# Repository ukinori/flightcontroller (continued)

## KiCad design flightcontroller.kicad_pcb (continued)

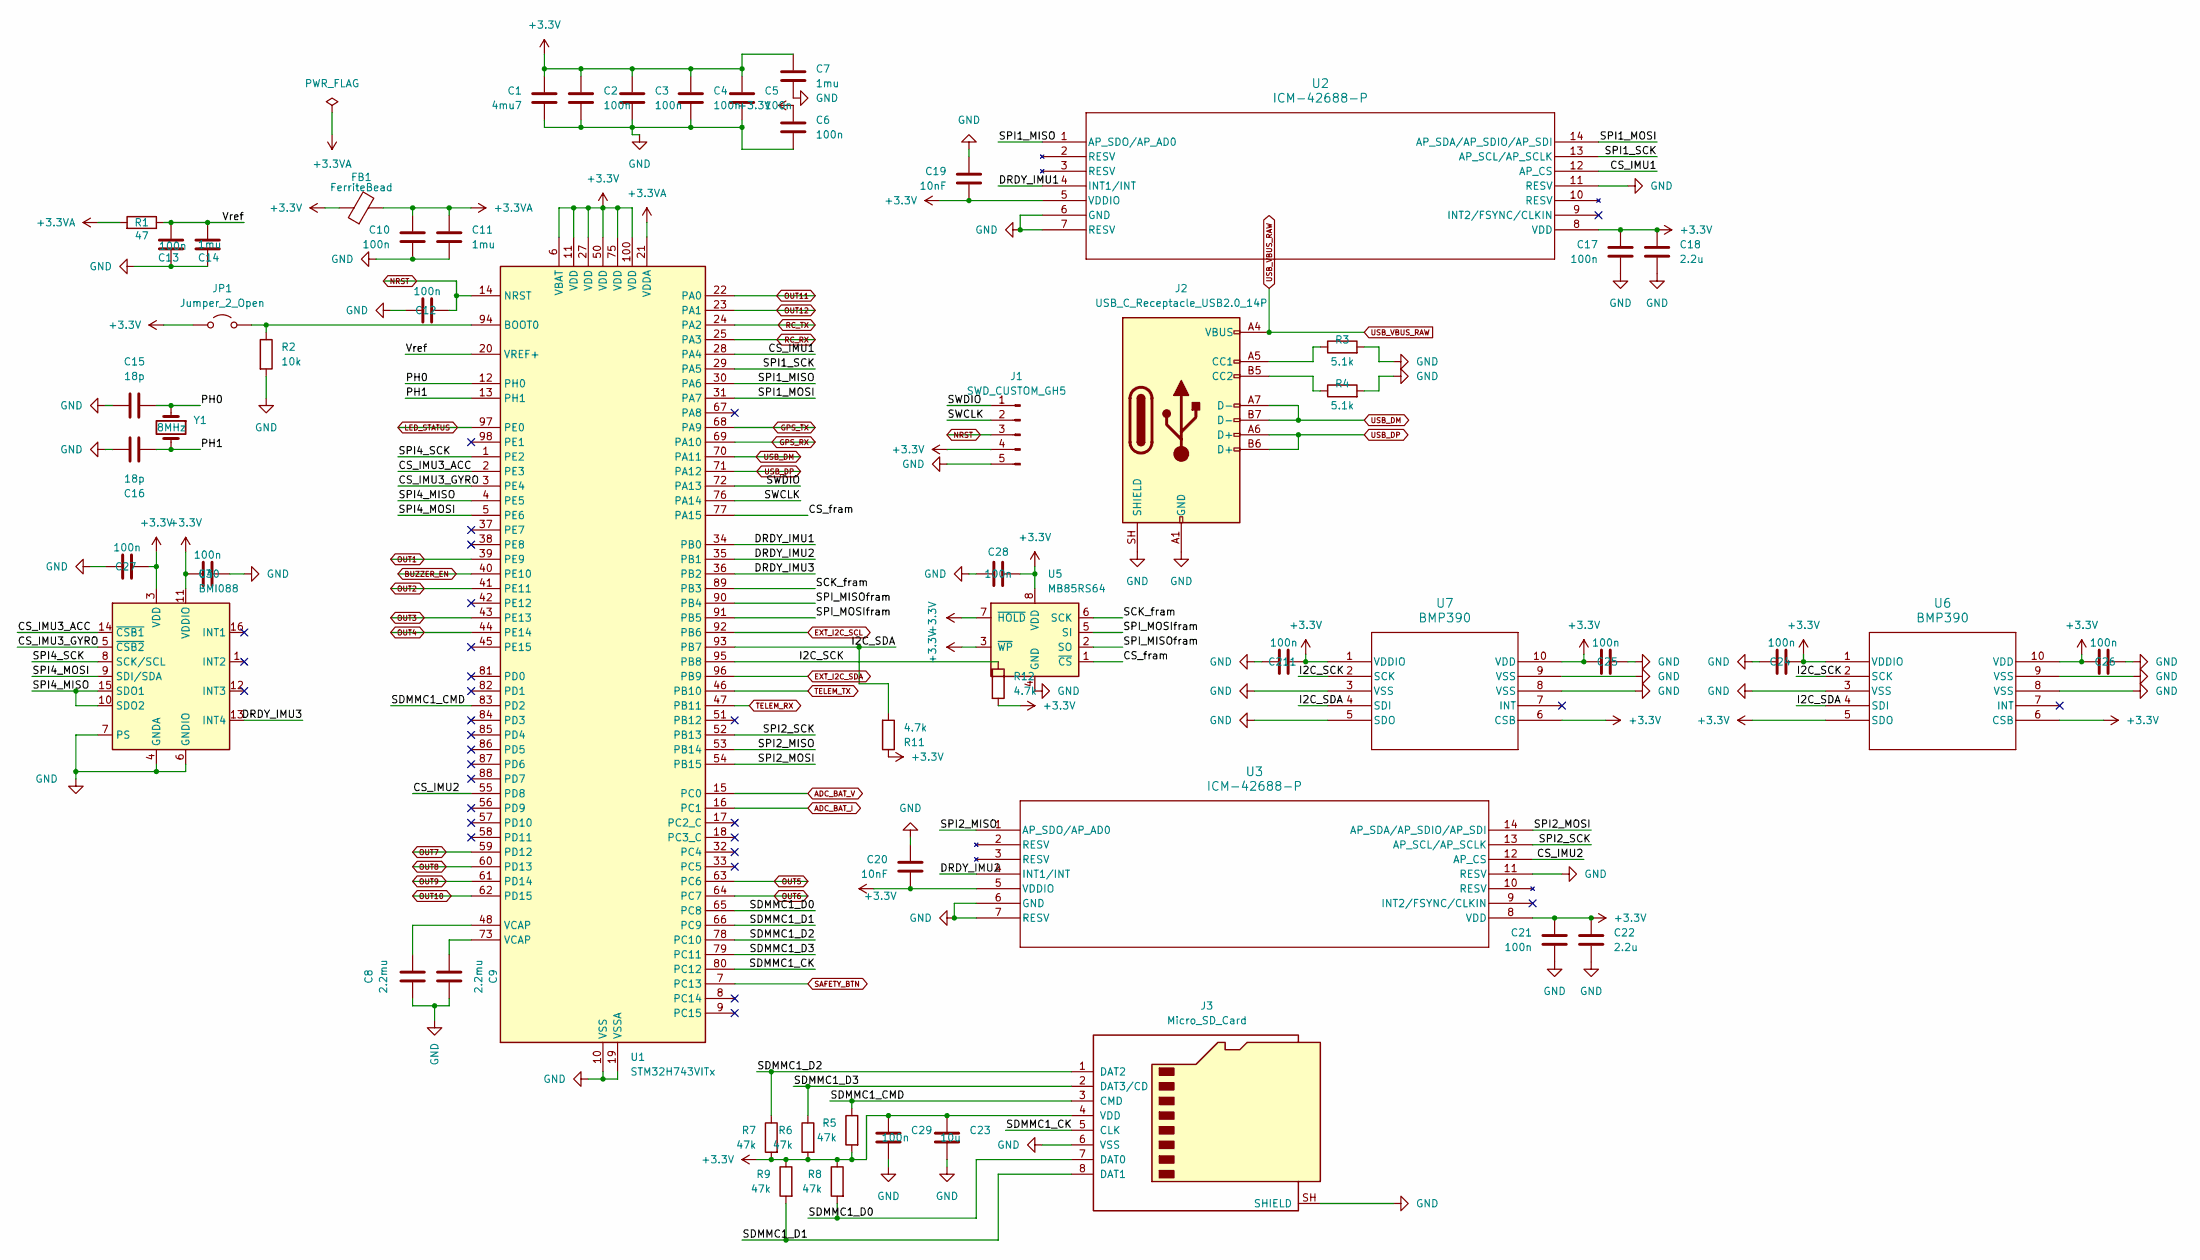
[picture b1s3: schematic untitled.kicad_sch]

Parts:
C1: 4mu7; C_0805_2012Metric
C2, C3, C4, C5, C6, C10, C12, C13, C24, C25, C26, C27, C29, C30, C211: 100n; C_0603_1608Metric
C7, C11, C14: 1mu; C_0603_1608Metric
C8, C9: 2.2mu; C_0805_2012Metric
C15, C16: 18p; C_0603_1608Metric; Voltage 50V; Tolerance 5%; MPN GRM1885C1H180JA01D
C17, C21, C28: 100n; C_0603_1608Metric; Voltage 25V; Tolerance 10%; MPN GRM188R71E104KA01D
C18, C22: 2.2u; C_0805_2012Metric; Voltage 16V; Tolerance 10%; MPN GRM21BR71C225KA12L
C19, C20: 10nF; C_0603_1608Metric
C23: 10u; C_0805_2012Metric
FB1: FerriteBead; L_0603_1608Metric; MPN BLM18PG121SN1D
J1: SWD_CUSTOM_GH5; JST_GH_SM05B-GHS-TB_1x05-1MP_P1.25mm_Horizontal
J2: USB_C_Receptacle_USB2.0_14P; USB_C_Receptacle_GCT_USB4105-xx-A_16P_TopMnt_Horizontal; MPN USB4105-GF-A
J3: Micro_SD_Card; microSD_HC_Hirose_DM3AT-SF-PEJM5; MPN DM3AT-SF-PEJM5
JP1: Jumper_2_Open; PinHeader_1x02_P2.54mm_Vertical
R1: 47; R_0603_1608Metric
R2: 10k; R_0603_1608Metric
R3, R4: 5.1k; R_0603_1608Metric
R5, R6, R7, R8, R9: 47k; R_0603_1608Metric
R11, R12: 4.7k; R_0603_1608Metric
U1: STM32H743VITx; LQFP-100_14x14mm_P0.5mm
U2, U3: ICM-42688-P; LGA14_2P5X3X0P91_TDK
U4: BMI088; Bosch_LGA-16_4.5x3mm_P0.5mm_LayoutBorder7x1y_ClockwisePinNu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
U5: MB85RS64; SOIC-8_3.9x4.9mm_P1.27mm; MPN MB85RS64PNF-G-JNE1
U6, U7: BMP390; 10LGA_2X2X0p75_BOS
Y1: 8MHz; Crystal_SMD_Abracon_ABM3-2Pin_5.0x3.2mm; MPN ABM3-8.000MHZ-12-D4Y-T

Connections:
+3.3V: C1.1, C2.1, C3.1, C4.1, C5.1, C6.1, C7.1, C17.1, C18.1, C19.2, C20.2, C21.1, C22.1, C23.1, C24.1, C25.1, C26.1, C27.1, C28.2, C29.1, C30.1, C211.1, FB1.1, J1.4, J3.4 (VDD), JP1.1 (A), R5.2, R6.2, R7.2, R8.1, R9.1, R11.1, R12.2, U1.6 (VBAT), U1.11 (VDD), U1.27 (VDD), U1.50 (VDD), U1.75 (VDD), U1.100 (VDD), U2.5 (VDDIO), U2.8 (VDD), U3.5 (VDDIO), U3.8 (VDD), U4.3 (VDD), U4.11 (VDDIO), U5.3 (~WP), U5.7 (~HOLD), U5.8 (VDD), U6.1 (VDDIO), U6.5 (SDO), U6.6 (CSB), U6.10 (VDD), U7.1 (VDDIO), U7.6 (CSB), U7.10 (VDD); also elsewhere on the board
+3.3VA: C10.1, C11.1, FB1.2, R1.2, U1.21 (VDDA)
/MCU/CS_IMU1: U1.28 (PA4), U2.12 (AP_CS)
/MCU/CS_IMU2: U1.55 (PD8), U3.12 (AP_CS)
/MCU/CS_IMU3_ACC: U1.2 (PE3), U4.14 (~CSB1)
/MCU/CS_IMU3_GYRO: U1.3 (PE4), U4.5 (~CSB2)
/MCU/CS_fram: U1.77 (PA15), U5.1 (~CS)
/MCU/DRDY_IMU1: U1.34 (PB0), U2.4 (INT1/INT)
/MCU/DRDY_IMU2: U1.35 (PB1), U3.4 (INT1/INT)
/MCU/DRDY_IMU3: U1.36 (PB2), U4.13 (INT4)
/MCU/I2C_SCK: R12.1, U1.95 (PB8), U6.2 (SCK), U7.2 (SCK)
/MCU/I2C_SDA: R11.2, U1.93 (PB7), U6.4 (SDI), U7.4 (SDI)
/MCU/PH0: C15.1, U1.12 (PH0), Y1.1
/MCU/PH1: C16.1, U1.13 (PH1), Y1.2
/MCU/SCK_fram: U1.89 (PB3), U5.6 (SCK)
/MCU/SDMMC1_CK: J3.5 (CLK), U1.80 (PC12)
/MCU/SDMMC1_CMD: J3.3 (CMD), R5.1, U1.83 (PD2)
/MCU/SDMMC1_D0: J3.7 (DAT0), R8.2, U1.65 (PC8)
/MCU/SDMMC1_D1: J3.8 (DAT1), R9.2, U1.66 (PC9)
/MCU/SDMMC1_D2: J3.1 (DAT2), R7.1, U1.78 (PC10)
/MCU/SDMMC1_D3: J3.2 (DAT3/CD), R6.1, U1.79 (PC11)
/MCU/SPI1_MISO: U1.30 (PA6), U2.1 (AP_SDO/AP_AD0)
/MCU/SPI1_MOSI: U1.31 (PA7), U2.14 (AP_SDA/AP_SDIO/AP_SDI)
/MCU/SPI1_SCK: U1.29 (PA5), U2.13 (AP_SCL/AP_SCLK)
/MCU/SPI2_MISO: U1.53 (PB14), U3.1 (AP_SDO/AP_AD0)
/MCU/SPI2_MOSI: U1.54 (PB15), U3.14 (AP_SDA/AP_SDIO/AP_SDI)
/MCU/SPI2_SCK: U1.52 (PB13), U3.13 (AP_SCL/AP_SCLK)
/MCU/SPI4_MISO: U1.4 (PE5), U4.10 (SDO2), U4.15 (SDO1)
/MCU/SPI4_MOSI: U1.5 (PE6), U4.9 (SDI/SDA)
/MCU/SPI4_SCK: U1.1 (PE2), U4.8 (SCK/SCL)
/MCU/SPI_MISOfram: U1.90 (PB4), U5.2 (SO)
/MCU/SPI_MOSIfram: U1.91 (PB5), U5.5 (SI)
/MCU/SWCLK: J1.2, U1.76 (PA14)
/MCU/SWDIO: J1.1, U1.72 (PA13)
/MCU/Vref: C13.1, C14.1, R1.1, U1.20 (VREF+)
ADC_BAT_I: U1.16 (PC1); also elsewhere on the board
ADC_BAT_V: U1.15 (PC0); also elsewhere on the board
BUZZER_EN: U1.40 (PE10); also elsewhere on the board
EXT_I2C_SCL: U1.92 (PB6); also elsewhere on the board
EXT_I2C_SDA: U1.96 (PB9); also elsewhere on the board
GND: C1.2, C2.2, C3.2, C4.2, C5.2, C6.2, C7.2, C8.2, C9.2, C10.2, C11.2, C12.2, C13.2, C14.2, C15.2, C16.2, C17.2, C18.2, C19.1, C20.1, C21.2, C22.2, C23.2, C24.2, C25.2, C26.2, C27.2, C28.1, C29.2, C30.2, C211.2, J1.5, J2.A1 (GND), J2.A12 (GND), J2.B1 (GND), J2.B12 (GND), J2.SH (SHIELD), J3.6 (VSS), J3.SH (SHIELD), R2.2, R3.2, R4.2, U1.10 (VSS), U1.19 (VSSA), U1.26 (VSS), U1.49 (VSS), U1.74 (VSS), U1.99 (VSS), U2.6 (GND), U2.7 (RESV), U2.11 (RESV), U3.6 (GND), U3.7 (RESV), U3.11 (RESV), U4.2 (GNDA), U4.4 (GNDA), U4.6 (GNDIO), U4.7 (PS), U5.4 (GND), U6.3 (VSS), U6.8 (VSS), U6.9 (VSS), U7.3 (VSS), U7.5 (SDO), U7.8 (VSS), U7.9 (VSS); also elsewhere on the board
GPS_RX: U1.69 (PA10); also elsewhere on the board
GPS_TX: U1.68 (PA9); also elsewhere on the board
LED_STATUS: U1.97 (PE0); also elsewhere on the board
NRST: C12.1, J1.3, U1.14 (NRST); also elsewhere on the board
unnamed: C8.1, U1.48 (VCAP)
unnamed: C9.1, U1.73 (VCAP)
unnamed: J2.A5 (CC1), R3.1
unnamed: J2.B5 (CC2), R4.1
unnamed: JP1.2 (B), R2.1, U1.94 (BOOT0)
OUT1: U1.39 (PE9); also elsewhere on the board
OUT2: U1.41 (PE11); also elsewhere on the board
OUT3: U1.43 (PE13); also elsewhere on the board
OUT4: U1.44 (PE14); also elsewhere on the board
OUT5: U1.63 (PC6); also elsewhere on the board
OUT6: U1.64 (PC7); also elsewhere on the board
OUT7: U1.59 (PD12); also elsewhere on the board
OUT8: U1.60 (PD13); also elsewhere on the board
OUT9: U1.61 (PD14); also elsewhere on the board
OUT10: U1.62 (PD15); also elsewhere on the board
OUT11: U1.22 (PA0); also elsewhere on the board
OUT12: U1.23 (PA1); also elsewhere on the board
RC_RX: U1.25 (PA3); also elsewhere on the board
RC_TX: U1.24 (PA2); also elsewhere on the board
SAFETY_BTN: U1.7 (PC13); also elsewhere on the board
TELEM_RX: U1.47 (PB11); also elsewhere on the board
TELEM_TX: U1.46 (PB10); also elsewhere on the board
USB_DM: J2.A7 (D-), J2.B7 (D-), U1.70 (PA11); also elsewhere on the board
USB_DP: J2.A6 (D+), J2.B6 (D+), U1.71 (PA12); also elsewhere on the board
USB_VBUS_RAW: J2.A4 (VBUS), J2.A9 (VBUS), J2.B4 (VBUS), J2.B9 (VBUS); also elsewhere on the board

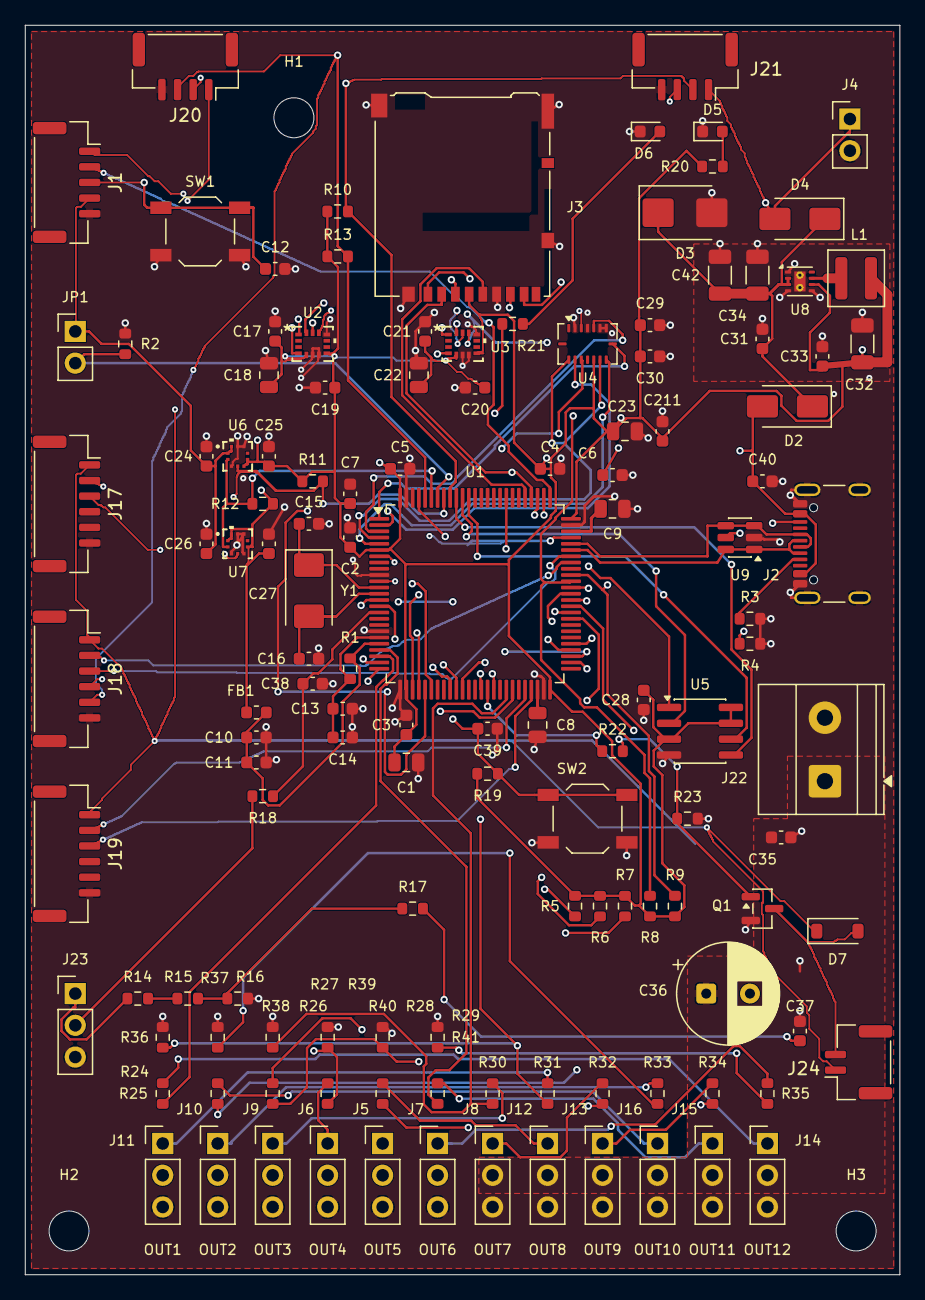
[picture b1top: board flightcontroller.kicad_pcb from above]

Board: 4 copper layers, 70.0 x 100.0 mm, 132 parts (0 on the bottom side), 94 nets.

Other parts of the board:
H1, H2, H3: M3; MountingHole_3.2mm_M3
